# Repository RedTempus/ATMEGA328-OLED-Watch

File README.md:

# ATMEGA328-OLED-Watch
Building a reprogrammable watch around the ATMEGA328 microcontroller, with a OLED screen, and running it off of a CR2450 battery.

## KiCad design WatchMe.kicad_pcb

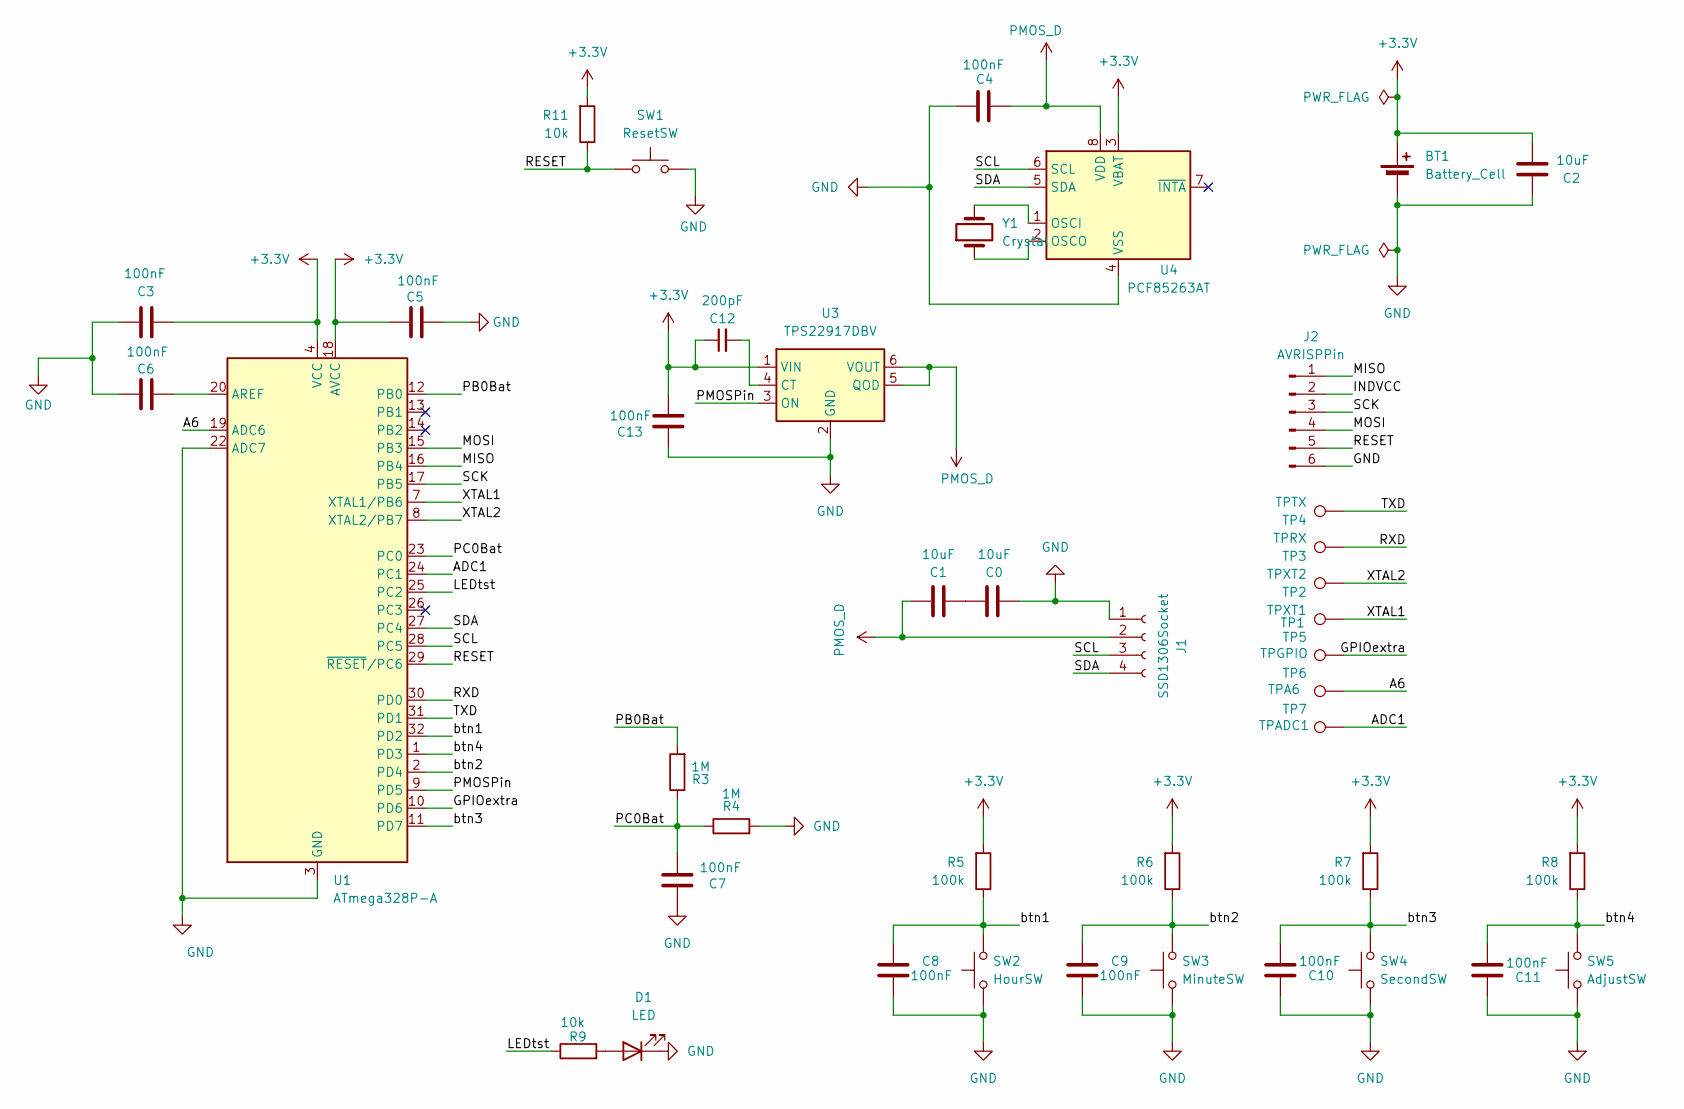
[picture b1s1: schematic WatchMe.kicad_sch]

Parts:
BT1: Battery_Cell; CR2450Holder
C0, C1, C2: 10uF; C_0805_2012Metric_Pad1.18x1.45mm_HandSolder
C3, C4, C5, C6, C7, C8, C9, C10, C11, C13: 100nF; C_0805_2012Metric_Pad1.18x1.45mm_HandSolder
C12: 200pF; C_0805_2012Metric_Pad1.18x1.45mm_HandSolder
D1: LED; LED_0805_2012Metric_Pad1.15x1.40mm_HandSolder
J1: SSD1306Socket
J2: AVRISPPin; PinHeader_2x03_P2.54mm_Vertical
R3, R4: 1M; R_0603_1608Metric_Pad0.98x0.95mm_HandSolder
R5, R6, R7, R8: 100k; R_0603_1608Metric_Pad0.98x0.95mm_HandSolder
R9, R11: 10k; R_0603_1608Metric_Pad0.98x0.95mm_HandSolder
SW1: ResetSW; SWT7016
SW2: HourSW; SWT7016
SW3: MinuteSW; SWT7016
SW4: SecondSW; SWT7016
SW5: AdjustSW; SWT7016
TP1: TPXT1; TestPoint_Pad_D2.0mm
TP2: TPXT2; TestPoint_Pad_D2.0mm
TP3: TPRX; TestPoint_Pad_D2.0mm
TP4: TPTX; TestPoint_Pad_D2.0mm
TP5: TPGPIO; TestPoint_Pad_D2.0mm
TP6: TPA6; TestPoint_Pad_D2.0mm
TP7: TPADC1; TestPoint_Pad_D2.0mm
U1: ATmega328P-A; TQFP-32_7x7mm_P0.8mm
U3: TPS22917DBV; SOT-23-6
U4: PCF85263AT; SOIC-8_3.9x4.9mm_P1.27mm
Y1: Crystal; Crystal_DS26_D2.0mm_L6.0mm_Horizontal

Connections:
+3.3V: BT1.1 (+), C2.1, C3.2, C5.2, C12.1, C13.2, R5.2, R6.2, R7.2, R8.2, R11.2, U1.4 (VCC), U1.6 (VCC), U1.18 (AVCC), U3.1 (VIN), U4.3 (VBAT)
/A6: TP6.1, U1.19 (ADC6)
/ADC1: TP7.1, U1.24 (PC1)
/GPIOextra: TP5.1, U1.10 (PD6)
/INDVCC: J2.2
/LEDtst: R9.1, U1.25 (PC2)
/MISO: J2.1, U1.16 (PB4)
/MOSI: J2.4, U1.15 (PB3)
/PB0Bat: R3.2, U1.12 (PB0)
/PC0Bat: C7.1, R3.1, R4.1, U1.23 (PC0)
/PMOSPin: U1.9 (PD5), U3.3 (ON)
/RESET: J2.5, R11.1, SW1.1, U1.29 (~RESET/PC6)
/RXD: TP3.1, U1.30 (PD0)
/SCK: J2.3, U1.17 (PB5)
/SCL: J1.3, U1.28 (PC5), U4.6 (SCL)
/SDA: J1.4, U1.27 (PC4), U4.5 (SDA)
/TXD: TP4.1, U1.31 (PD1)
/XTAL1: TP1.1, U1.7 (XTAL1/PB6)
/XTAL2: TP2.1, U1.8 (XTAL2/PB7)
/btn1: C8.1, R5.1, SW2.2, U1.32 (PD2)
/btn2: C9.1, R6.1, SW3.2, U1.2 (PD4)
/btn3: C10.1, R7.1, SW4.2, U1.11 (PD7)
/btn4: C11.1, R8.1, SW5.2, U1.1 (PD3)
GND: BT1.2 (-), C0.1, C2.2, C3.1, C4.2, C5.1, C6.1, C7.2, C8.2, C9.2, C10.2, C11.2, C13.1, D1.1 (K), J1.1, J2.6, R4.2, SW1.2, SW2.1, SW3.1, SW4.1, SW5.1, U1.3 (GND), U1.5 (GND), U1.21 (GND), U1.22 (ADC7), U3.2 (GND), U4.4 (VSS)
unnamed: C0.2, C1.1
unnamed: D1.2 (A), R9.2
unnamed: C6.2, U1.20 (AREF)
unnamed: C12.2, U3.4 (CT)
unnamed: U4.1 (OSCI), Y1.2
unnamed: U4.2 (OSCO), Y1.1
PMOS_D: C1.2, C4.1, J1.2, U3.5 (QOD), U3.6 (VOUT), U4.8 (VDD)

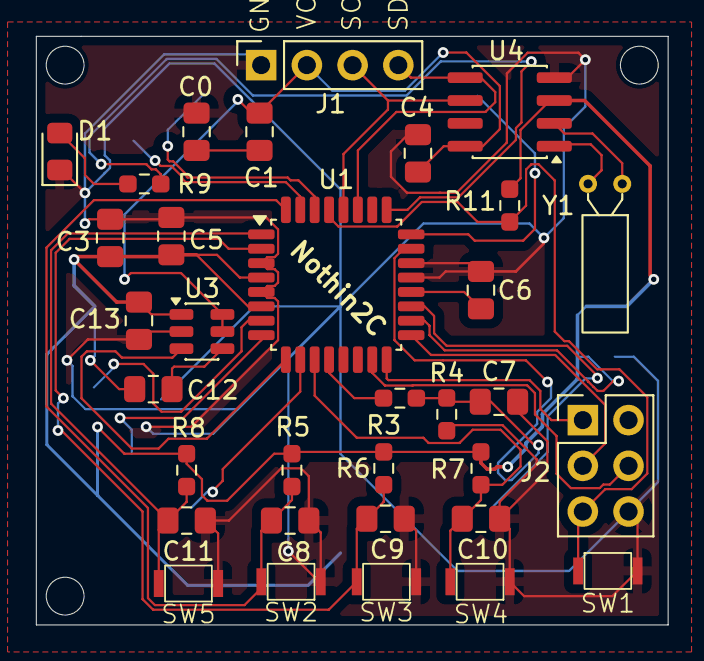
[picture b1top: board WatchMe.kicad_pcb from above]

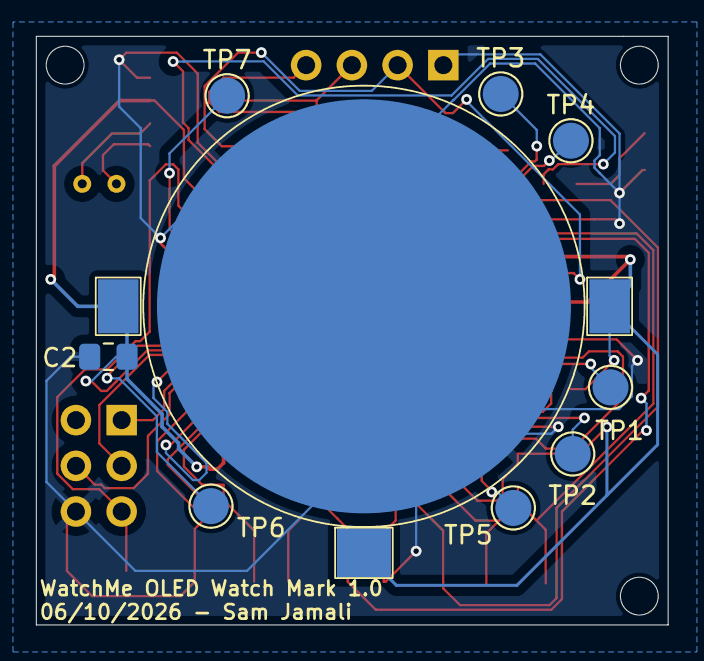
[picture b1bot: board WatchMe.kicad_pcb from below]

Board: 4 copper layers, 35.1 x 32.7 mm, 42 parts (9 on the bottom side), 30 nets.
